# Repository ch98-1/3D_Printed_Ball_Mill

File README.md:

# 3D_Printed_Ball_Mill
 3d printed ball mill

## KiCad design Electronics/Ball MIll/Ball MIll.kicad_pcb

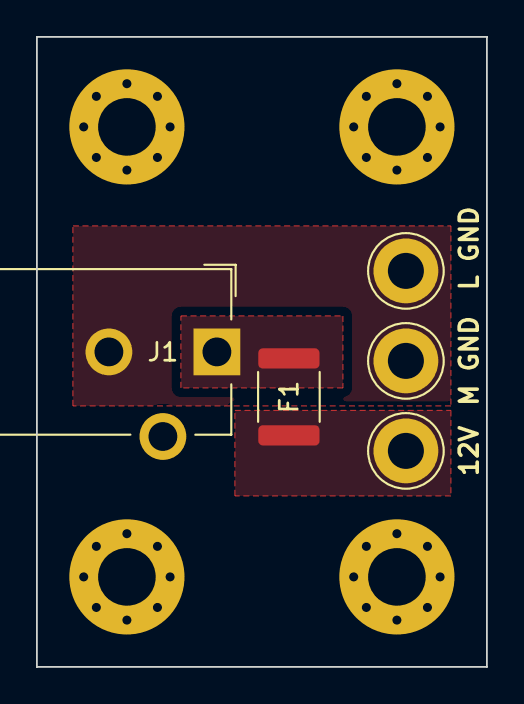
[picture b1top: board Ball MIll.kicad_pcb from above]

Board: 2 copper layers, 25.0 x 35.0 mm, 9 parts (0 on the bottom side), 3 nets, no tracks yet.

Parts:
F1: Polyfuse; R_1812_4532Metric
H1, H2, H3, H4: MountingHole; MountingHole_3.2mm_M3_Pad_Via
J1: Jack-DC; BarrelJack_CUI_PJ-102AH_Horizontal
J2, J3, J4: Conn_01x01; TestPoint_Loop_D3.80mm_Drill2.0mm

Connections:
unnamed: F1.1, J2.1
unnamed: F1.2, J1.1
unnamed: J1.2, J3.1, J4.1

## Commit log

2020-08-18 Made PCB
2020-08-18 Created the jar model
2020-08-18 Fixed an error on the seal
2020-08-18 Added processed and oriented print files for easier printing
2020-08-19 Added shaft and pin
2020-08-20 Finished the v1 of the design
2020-08-21 Updated print settings
2020-08-21 podated pcb
2020-08-22 updated the chassis for better printability and updated BOM
